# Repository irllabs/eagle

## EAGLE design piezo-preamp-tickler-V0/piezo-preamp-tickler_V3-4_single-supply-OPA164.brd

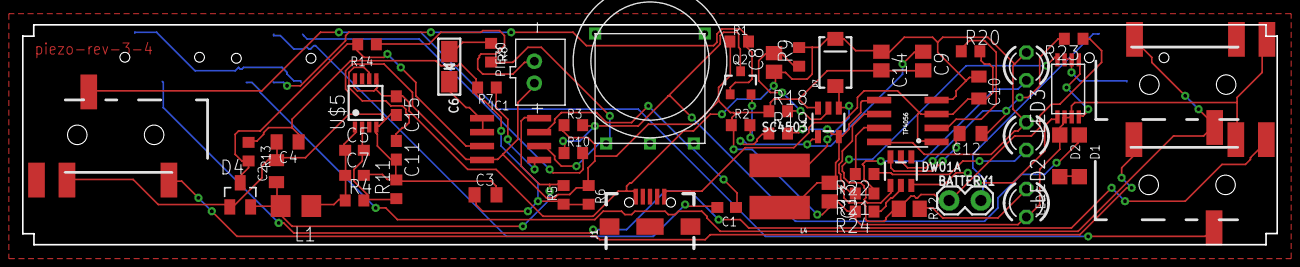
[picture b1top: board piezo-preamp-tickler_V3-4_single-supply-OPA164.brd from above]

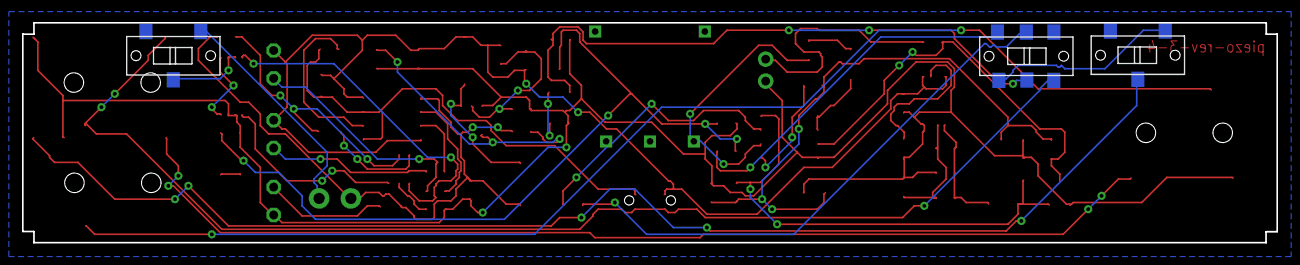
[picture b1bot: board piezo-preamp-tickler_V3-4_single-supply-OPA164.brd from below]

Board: 2 copper layers, 114.3 x 20.0 mm, 62 parts (3 on the bottom side), 44 nets.

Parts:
BATTERY1: 1X02_LOCK
C1, C7, C15: 10uF; C0603
C2, C4, C10, C12: 0.1uF; C0805K
C3: 10uF; C0805K
C5, C11: 10nF; C0603
C6: 100uF; EIA3216-18/A-R
C8: 2.2pf; C0805
C9: 56nf; C0805
C13: 10uF; C0805
C14: 68uF; C0805
D1, D2: SOD123
D4: BAT54S; SOT23
D7: 10BQ015; SMA-DIODE
DW01A: DW01A; SOT23-6
F8205A: F8205A
IC1: OPA1642; SO08
J1: USB-B-MICRO-SMD_RED_PASTE
L1: 100uH; L3225P
L4: 2.7uH; CR54
LED1, LED2, LED3: LED3MM
PIEZO: JST-PH-2-THM
POWER: SPDT; SWITCH_SPDT_CL-SB-12B
Q2: MMBFJ201; SOT23-3
R1: 2.2K; R0603
R2: 1.2K; R0603
R3, R9: 1M; R0603
R4: 91.2k; R0603
R5, R6, R14: 100K; R0603
R7, R8: 220; R0603
R10: 1K; R0603
R11, R18: 100k; R0603
R12: 390; R0805
R13: 10M; R0603
R19: 15k; R0603
R20: 1.2k; R0603
R21, R22: 1k; R0603
R23: nfo; R0603
R24: 100; R0603
SC4503: VREG12_SOT23-5; SOT23-5
SW2-SPST: INPUT-select; SWITCH_SPDT_CL-SB-12B
TO-HEADSET: AUDIO-JACK3LGPADS; AUDIO-JACK-TRRS-SMD
TO-PHONE, TO-PHONE1: AUDIO-JACK3LGPADS; AUDIO-JACK-TRRS-SMD
TP4056: TP4056-CHIP; SO08
U$2: SWITCH_DPDT; SWITCH_DPDT_CL-SB-22B
U$4: POT-THUMB-14MM_ALPHA-RV100F-30-4K1B-B10K-B301
U$5: TPS7A49; MSOP-8

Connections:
+12V: C5.1, C7.1, L1.1, R4.1, U$5.1
GND: C2.2, C3.2, C4.2, C7.2, C9.2, C11.2, C13.2, C14.2, C15.2, D2.C, D4.1, F8205A.P$6, F8205A.P$7, IC1.4, LED1.K, PIEZO.1, R1.1, R2.1, R3.1, R6.1, R11.2, R18.1, R24.2, SC4503.3, TO-HEADSET.RING2, TO-PHONE.RING2, TO-PHONE1.EARTH, U$5.4
unnamed: D1.A, D2.A
unnamed: PIEZO.2, R14.1
unnamed: Q2.2, R2.2
unnamed: IC1.5, R7.1
unnamed: C1.1, IC1.7, U$4.P$3
unnamed: IC1.6, R8.2, U$4.P$1
unnamed: D4.3, IC1.3, R13.2, R14.2
unnamed: D1.C, Q2.3, R3.2, R10.1
unnamed: R10.2, U$2.4
unnamed: TO-PHONE1.RING1, TO-PHONE1.TIP, U$2.3
unnamed: TO-HEADSET.TIP, TO-PHONE.TIP
unnamed: C6.-, R8.1
unnamed: TO-HEADSET.RING1, TO-PHONE.RING1
unnamed: C1.2, U$2.5
unnamed: SW2-SPST.P$2, TO-PHONE.EARTH
unnamed: LED1.A, R12.1
unnamed: SW2-SPST.P$1, U$2.1
unnamed: F8205A.P$2, F8205A.P$3, POWER.P$2
unnamed: BATTERY1.2, POWER.P$1
unnamed: C3.1, C4.1, R5.1, R6.2, R7.2, R13.1
unnamed: C6.+, IC1.1, IC1.2
unnamed: C2.1, D4.2, IC1.8, L1.2, R5.2
unnamed: C5.2, R4.2, R11.1, U$5.2
unnamed: C11.1, U$5.6
unnamed: C9.1, R19.1, SC4503.4
unnamed: C8.2, R9.1, R18.2, SC4503.2
unnamed: D7.A, L4.P$2, SC4503.1
unnamed: C10.2, J1.GND, R20.2, TP4056.1, TP4056.3
unnamed: DW01A.1, F8205A.P$4
unnamed: R20.1, TP4056.2
unnamed: DW01A.3, F8205A.P$5
unnamed: R22.2, TP4056.7
unnamed: R21.2, TP4056.6
unnamed: LED3.K, R21.1
unnamed: LED2.K, R22.1
unnamed: C12.1, DW01A.5, R23.2
unnamed: C12.2, DW01A.6
unnamed: DW01A.2, R24.1
unnamed: F8205A.P$1, F8205A.P$8
SELECT: Q2.1, R1.2, U$2.2
V+: C8.1, C10.1, C14.1, C15.1, D7.C, J1.VBUS, LED2.A, LED3.A, R9.2, TP4056.4, TP4056.8, U$5.5, U$5.8
VBAT: BATTERY1.1, C13.1, L4.P$1, R12.2, R19.2, R23.1, SC4503.5, TP4056.5

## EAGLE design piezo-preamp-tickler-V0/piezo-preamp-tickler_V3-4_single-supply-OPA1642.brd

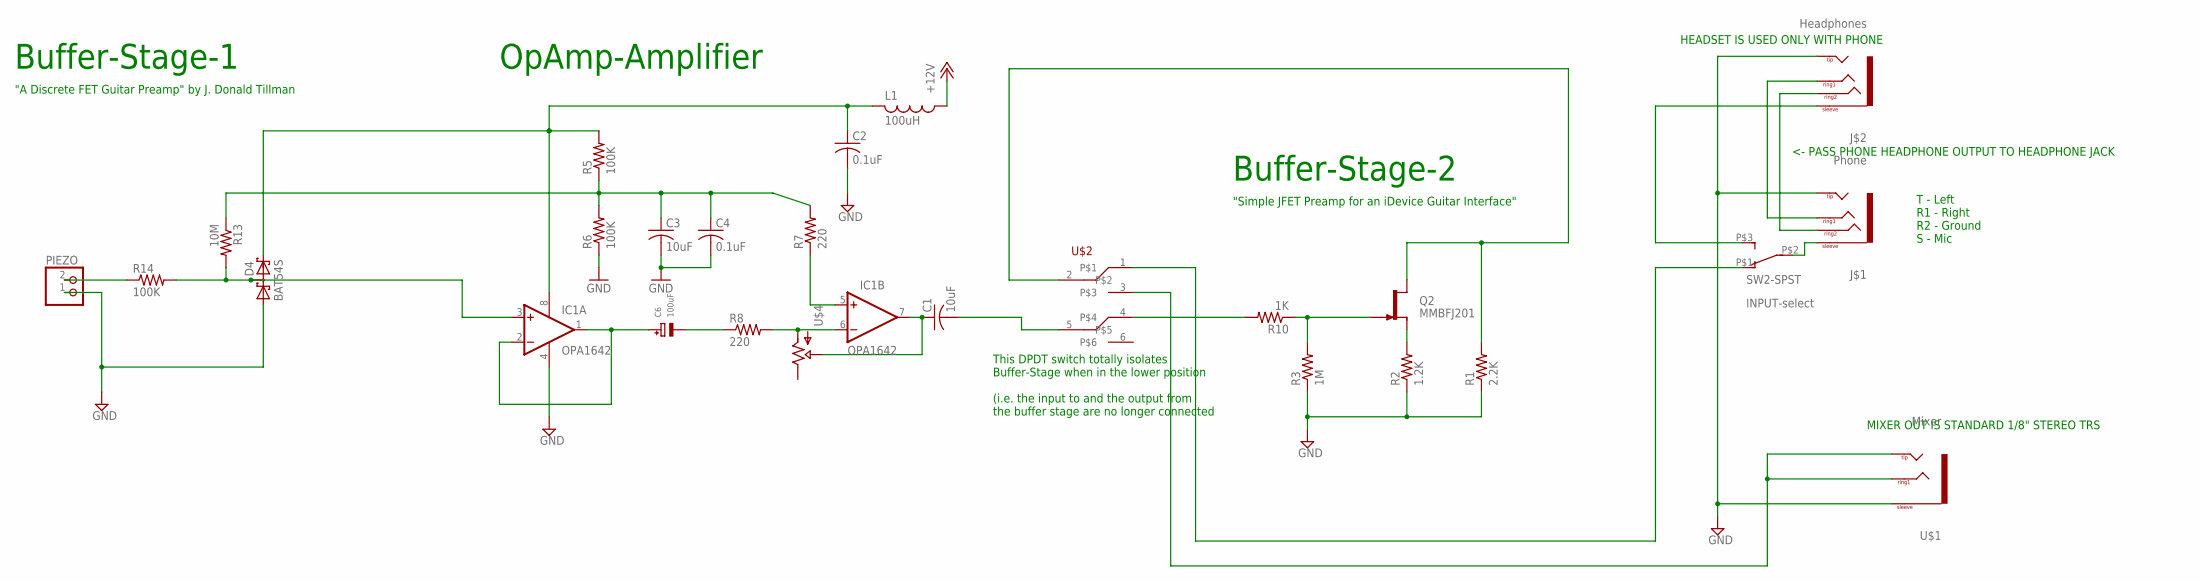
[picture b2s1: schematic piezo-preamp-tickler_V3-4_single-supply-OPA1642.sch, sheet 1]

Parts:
C1: 10uF; C0805
C2, C4: 0.1uF; C0805K
C3: 10uF; C0805K
C6: 100uF; EIA3216-18/A-R
D4: BAT54S; SOT23
IC1: OPA1642; SO08
J$1: Phone; TRRS_SJ-43514-SMT-TR
J$2: Headphones; TRRS_SJ-43514-SMT-TR
L1: 100uH; L3225P
PIEZO: JST_2PIN-THM; JST-PH-2-THM
Q2: MMBFJ201; SOT23-3
R1: 2.2K; R0603
R2: 1.2K; R0603
R3: 1M; R0603
R5, R6, R14: 100K; R0603
R7, R8: 220; R0603
R10: 1K; R0603
R13: 10M; R0603
SW2-SPST: INPUT-select; SWITCH_SPDT_CL-SB-12B
U$1: Mixer; TRS_SJ-3524-SMT
U$2: SWITCH_DPDT; SWITCH_DPDT_CL-SB-22B
U$4: POTPOT-THUMB-ALPHA; POT-THUMB-14MM_ALPHA-RV100F-30-4K1B-B10K-B301

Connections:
+12V: L1.1; also elsewhere on the board
GND: C2.2, C3.2, C4.2, D4.1 (A1), IC1.4 (V-), J$1.TIP, J$2.TIP, PIEZO.1 (2), R1.1, R2.1, R3.1, R6.1, U$1.1 (SLEEVE); also elsewhere on the board
unnamed: PIEZO.2 (1), R14.1
unnamed: Q2.2 (S), R2.2
unnamed: IC1.5 (+IN), R7.1
unnamed: C1.1, IC1.7 (OUT), U$4.P$3 (WIPER)
unnamed: IC1.6 (-IN), R8.2, U$4.P$1 (IN)
unnamed: D4.3 (C1A2), IC1.3 (+IN), R13.2, R14.2
unnamed: Q2.3 (G), R3.2, R10.1
unnamed: R10.2, U$2.4
unnamed: U$1.2 (TIP), U$1.3 (RING1), U$1.4 (TIP), U$2.3
unnamed: J$1.RING1, J$2.RING1
unnamed: C6.-, R8.1
unnamed: J$1.RING2, J$2.RING2
unnamed: C1.2, U$2.5
unnamed: J$1.EARTH (SLEEVE), SW2-SPST.P$2 (2)
unnamed: SW2-SPST.P$1 (1), U$2.1
unnamed: C3.1, C4.1, R5.1, R6.2, R7.2, R13.1
unnamed: C6.+, IC1.1 (OUT), IC1.2 (-IN)
unnamed: C2.1, D4.2 (C2), IC1.8 (V+), L1.2, R5.2
SELECT: Q2.1 (D), R1.2, U$2.2

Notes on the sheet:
Buffer-Stage-1
OpAmp-Amplifier
Buffer-Stage-2
"A Discrete FET Guitar Preamp" by J. Donald Tillman
"Simple JFET Preamp for an iDevice Guitar Interface"
T - Left R1 - Right R2 - Ground S - Mic
HEADSET IS USED ONLY WITH PHONE
MIXER OUT IS STANDARD 1/8" STEREO TRS
<- PASS PHONE HEADPHONE OUTPUT TO HEADPHONE JACK
This DPDT switch totally isolates Buffer-Stage when in the lower position (i.e. the input to and the output from the buffer stage are no longer connected

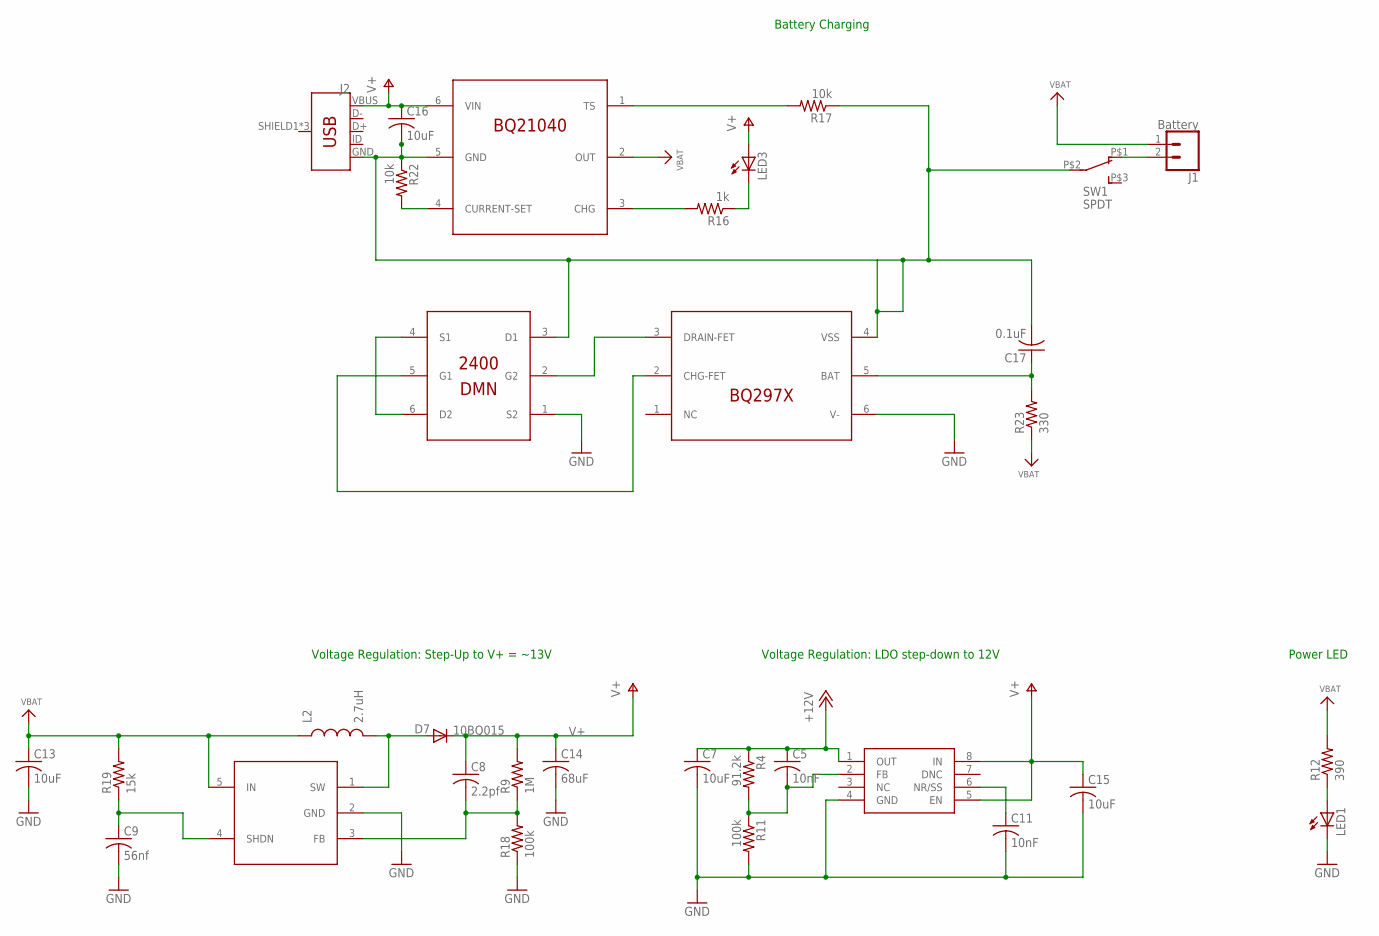
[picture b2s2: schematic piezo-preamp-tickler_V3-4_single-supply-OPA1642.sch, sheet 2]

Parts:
C5, C11: 10nF; C0603
C7, C13, C15: 10uF; C0603
C8: 2.2pf; C0603
C9: 56nf; C0603
C14: 68uF; C0603
C16: 10uF; C0805K
C17: 0.1uF; C0805K
D7: 10BQ015; SMA-DIODE
IC2: TPS7A49; MSOP-8
IC3: DMN2400; SOT-563
IC4: BQ297X; WSON-6
J1: Battery; 1X02_LOCK
J2: USB_MICRO-BREDUCED_PASTE; USB-B-MICRO-SMD_RED_PASTE
L2: 2.7uH; CR54
LED1, LED3: LED3MM
Q1: BQ21040; SOT23-6
Q3: SC4503; SOT23-5
R4: 91.2k; R0603
R9: 1M; R0603
R11, R18: 100k; R0603
R12: 390; R0805
R16: 1k; R0805
R17, R22: 10k; R0805
R19: 15k; R0603
R23: 330; R0805
SW1: SPDT; SWITCH_SPDT_CL-SB-12B

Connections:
+12V: C5.1, C7.1, IC2.1 (OUT), R4.1; also elsewhere on the board
GND: C7.2, C9.2, C11.2, C13.2, C14.2, C15.2, IC2.4 (GND), IC3.1 (S2), IC4.6 (V-), LED1.K (C), Q3.2 (GND), R11.2, R18.1; also elsewhere on the board
GND2: C16.2, C17.2, IC3.3 (D1), IC4.4 (VSS), J2.GND, Q1.5 (GND), R17.1, R22.1, SW1.P$2 (2)
unnamed: LED1.A, R12.1
unnamed: J1.2, SW1.P$1 (1)
unnamed: LED3.K (C), R16.1
unnamed: C5.2, IC2.2 (FB), R4.2, R11.1
unnamed: Q1.3 (CHG), R16.2
unnamed: C11.1, IC2.6 (NR/SS)
unnamed: C9.1, Q3.4 (SHDN), R19.1
unnamed: C8.2, Q3.3 (FB), R9.1, R18.2
unnamed: Q1.1 (TS), R17.2
unnamed: D7.A, L2.P$2 (2), Q3.1 (SW)
unnamed: Q1.4 (CURRENT-SET), R22.2
unnamed: C17.1, IC4.5 (BAT), R23.2
unnamed: IC3.4 (S1), IC3.6 (D2)
unnamed: IC3.5 (G1), IC4.2 (CHG-FET)
unnamed: IC3.2 (G2), IC4.3 (DRAIN-FET)
V+: C8.1, C14.1, C15.1, C16.1, D7.C, IC2.5 (EN), IC2.8 (IN), J2.VBUS, LED3.A, Q1.6 (VIN), R9.2
VBAT: C13.1, J1.1, L2.P$1 (1), Q1.2 (OUT), Q3.5 (IN), R12.2, R19.2, R23.1

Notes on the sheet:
Voltage Regulation: Step-Up to V+ = ~13V
Power LED
Voltage Regulation: LDO step-down to 12V
Battery Charging

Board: 2 copper layers, 58 parts (6 on the bottom side), 39 nets, no tracks yet.

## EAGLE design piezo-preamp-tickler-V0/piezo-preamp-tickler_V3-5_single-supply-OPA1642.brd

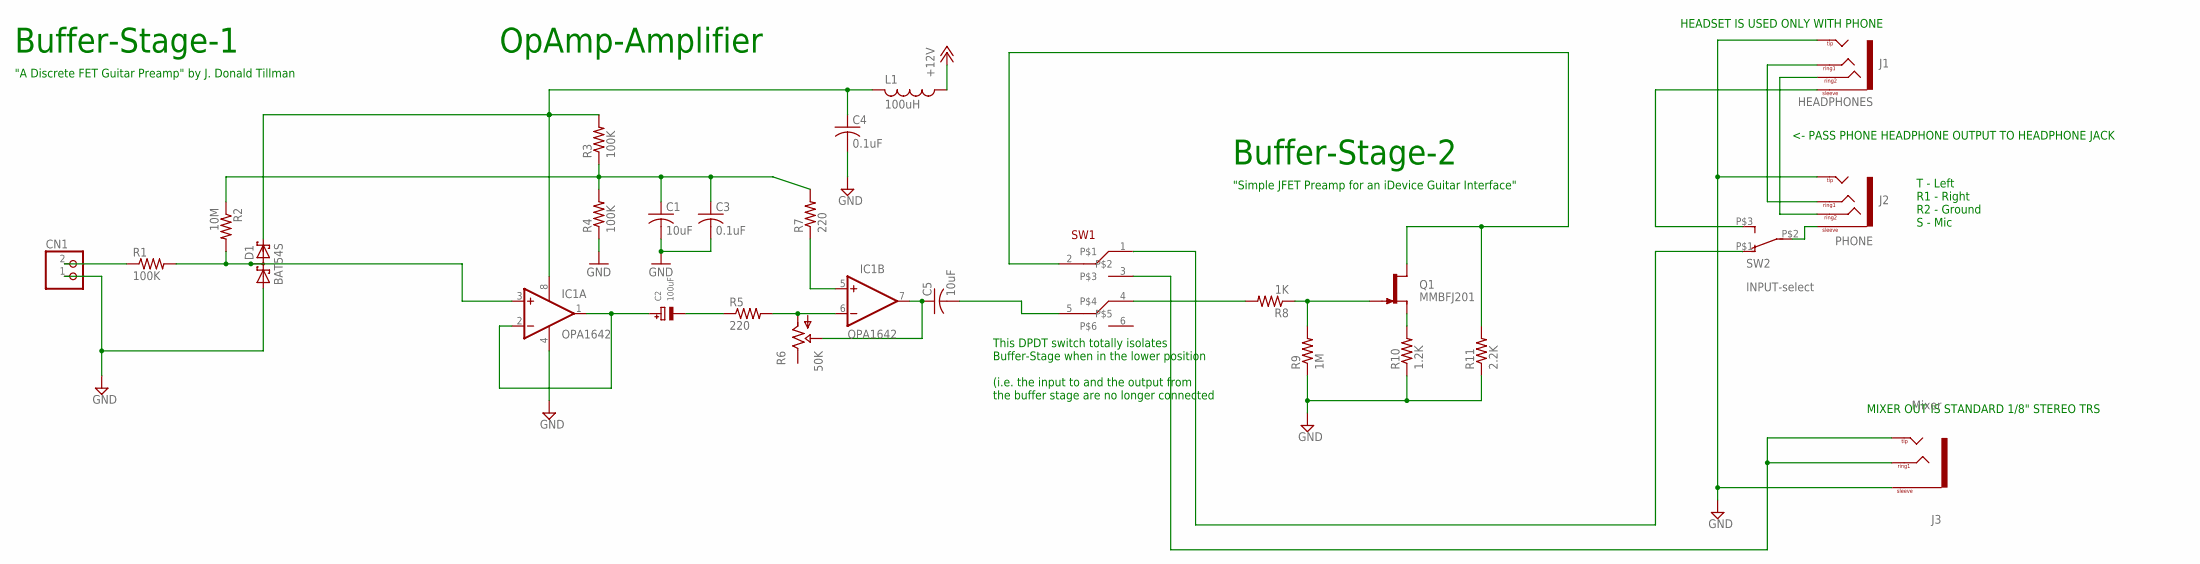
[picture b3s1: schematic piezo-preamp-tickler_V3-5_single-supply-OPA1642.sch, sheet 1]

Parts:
C1: 10uF; C0805K
C2: 100uF; EIA3216-18/A-R
C3, C4: 0.1uF; C0805K
C5: 10uF; C0805
CN1: JST_2PIN-THM; JST-PH-2-THM
D1: BAT54S; SOT23
IC1: OPA1642; SO08
J1: HEADPHONES; TRRS_SJ-43514-SMT-TR
J2: PHONE; TRRS_SJ-43514-SMT-TR
J3: Mixer; TRS_SJ-3524-SMT
L1: 100uH; L3225P
Q1: MMBFJ201; SOT23-3
R1, R3, R4: 100K; R0603
R2: 10M; R0603
R5, R7: 220; R0603
R6: 50K; POT-THUMB-14MM_ALPHA-RV100F-30-4K1B-B10K-B301
R8: 1K; R0603
R9: 1M; R0603
R10: 1.2K; R0603
R11: 2.2K; R0603
SW1: SWITCH_DPDT; SWITCH_DPDT_CL-SB-22B
SW2: INPUT-select; SWITCH_SPDT_CL-SB-12B

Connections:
+12V: L1.1; also elsewhere on the board
GND: C1.2, C3.2, C4.2, CN1.1 (2), D1.1 (A1), IC1.4 (V-), J1.TIP, J2.TIP, J3.1 (SLEEVE), R4.1, R9.1, R10.1, R11.1; also elsewhere on the board
unnamed: CN1.2 (1), R1.1
unnamed: Q1.2 (S), R10.2
unnamed: IC1.5 (+IN), R7.1
unnamed: C5.1, IC1.7 (OUT), R6.P$2 (WIPER)
unnamed: IC1.6 (-IN), R5.2, R6.P$1 (IN)
unnamed: D1.3 (C1A2), IC1.3 (+IN), R1.2, R2.2
unnamed: Q1.3 (G), R8.1, R9.2
unnamed: R8.2, SW1.4
unnamed: J3.2 (TIP), J3.3 (RING1), J3.4 (TIP), SW1.3
unnamed: J1.RING1, J2.RING1
unnamed: C2.-, R5.1
unnamed: J1.RING2, J2.RING2
unnamed: C5.2, SW1.5
unnamed: J2.EARTH (SLEEVE), SW2.P$2 (2)
unnamed: SW1.1, SW2.P$1 (1)
unnamed: C1.1, C3.1, R2.1, R3.1, R4.2, R7.2
unnamed: C2.+, IC1.1 (OUT), IC1.2 (-IN)
unnamed: C4.1, D1.2 (C2), IC1.8 (V+), L1.2, R3.2
SELECT: Q1.1 (D), R11.2, SW1.2

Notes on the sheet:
Buffer-Stage-1
OpAmp-Amplifier
Buffer-Stage-2
"A Discrete FET Guitar Preamp" by J. Donald Tillman
"Simple JFET Preamp for an iDevice Guitar Interface"
T - Left R1 - Right R2 - Ground S - Mic
HEADSET IS USED ONLY WITH PHONE
MIXER OUT IS STANDARD 1/8" STEREO TRS
<- PASS PHONE HEADPHONE OUTPUT TO HEADPHONE JACK
This DPDT switch totally isolates Buffer-Stage when in the lower position (i.e. the input to and the output from the buffer stage are no longer connected

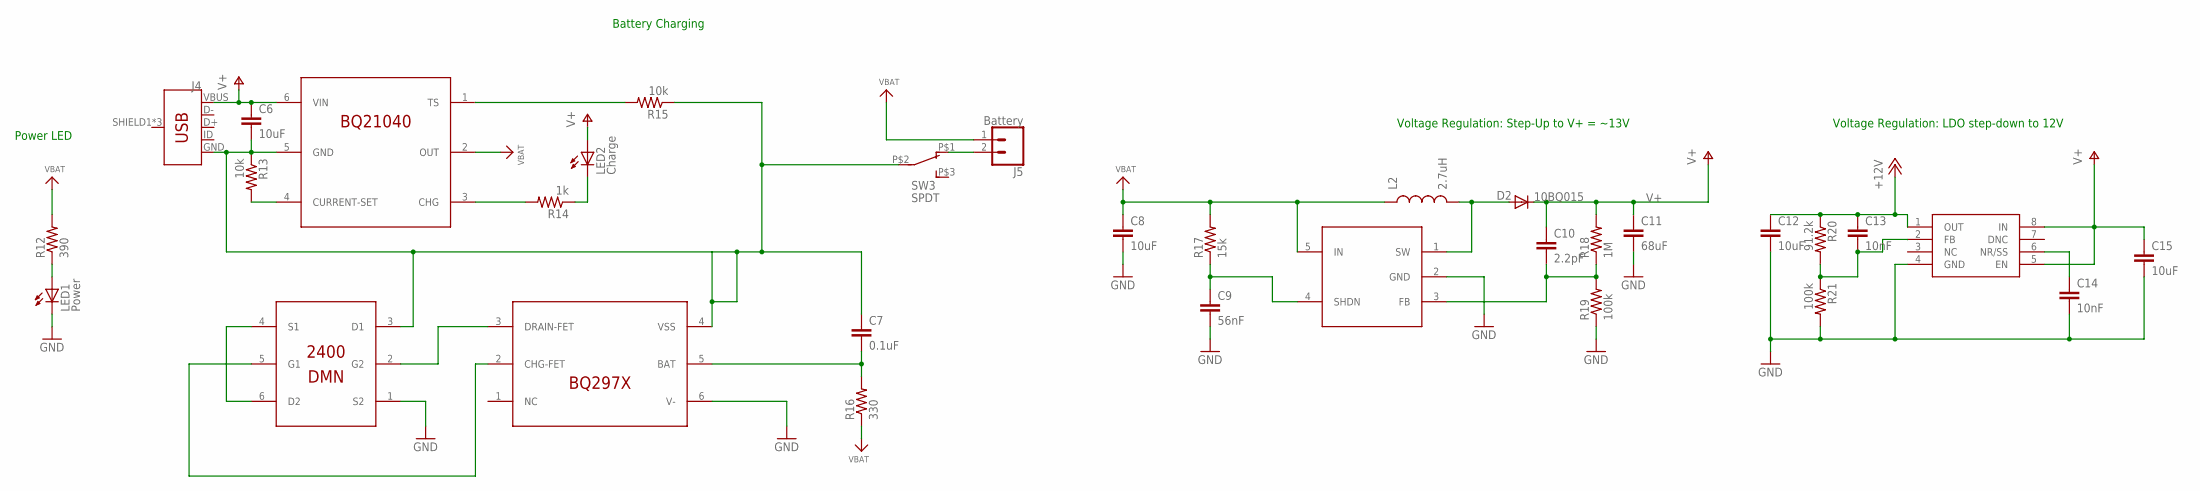
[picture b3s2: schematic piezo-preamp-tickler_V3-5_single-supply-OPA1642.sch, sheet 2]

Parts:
C6, C8, C12, C15: 10uF; C0603
C7: 0.1uF; C0603
C9: 56nF; C0603
C10: 2.2pF; C0603
C11: 68uF; C1206
C13, C14: 10nF; C0603
D2: 10BQ015; SMA-DIODE
IC2: DMN2400; SOT-563
IC3: BQ21040; SOT23-6
IC4: BQ297X; WSON-6
IC5: SC4503; SOT23-5
IC6: TPS7A49; MSOP-8
J4: USB_MICRO-BREDUCED_PASTE; USB-B-MICRO-SMD_RED_PASTE
J5: Battery; 1X02_LOCK
L2: 2.7uH; CR54
LED1: Power; LED3MM
LED2: Charge; LED3MM
R12: 390; R0603
R13, R15: 10k; R0603
R14: 1k; R0603
R16: 330; R0603
R17: 15k; R0603
R18: 1M; R0603
R19, R21: 100k; R0603
R20: 91.2k; R0603
SW3: SPDT; SWITCH_SPDT_CL-SB-12B

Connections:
+12V: C12.1, C13.1, IC6.1 (OUT), R20.1; also elsewhere on the board
GND: C8.2, C9.2, C11.2, C12.2, C14.2, C15.2, IC2.1 (S2), IC4.6 (V-), IC5.2 (GND), IC6.4 (GND), LED1.K (C), R19.1, R21.2; also elsewhere on the board
GND2: C6.2, C7.1, IC2.3 (D1), IC3.5 (GND), IC4.4 (VSS), J4.GND, R13.1, R15.1, SW3.P$2 (2)
unnamed: LED1.A, R12.1
unnamed: J5.2, SW3.P$1 (1)
unnamed: LED2.K (C), R14.1
unnamed: C13.2, IC6.2 (FB), R20.2, R21.1
unnamed: IC3.3 (CHG), R14.2
unnamed: C14.1, IC6.6 (NR/SS)
unnamed: C9.1, IC5.4 (SHDN), R17.1
unnamed: C10.2, IC5.3 (FB), R18.1, R19.2
unnamed: IC3.1 (TS), R15.2
unnamed: D2.A, IC5.1 (SW), L2.P$2 (2)
unnamed: IC3.4 (CURRENT-SET), R13.2
unnamed: C7.2, IC4.5 (BAT), R16.2
unnamed: IC2.4 (S1), IC2.6 (D2)
unnamed: IC2.5 (G1), IC4.2 (CHG-FET)
unnamed: IC2.2 (G2), IC4.3 (DRAIN-FET)
V+: C6.1, C10.1, C11.1, C15.1, D2.C, IC3.6 (VIN), IC6.5 (EN), IC6.8 (IN), J4.VBUS, LED2.A, R18.2
VBAT: C8.1, IC3.2 (OUT), IC5.5 (IN), J5.1, L2.P$1 (1), R12.2, R16.1, R17.2

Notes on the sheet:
Voltage Regulation: Step-Up to V+ = ~13V
Power LED
Voltage Regulation: LDO step-down to 12V
Battery Charging

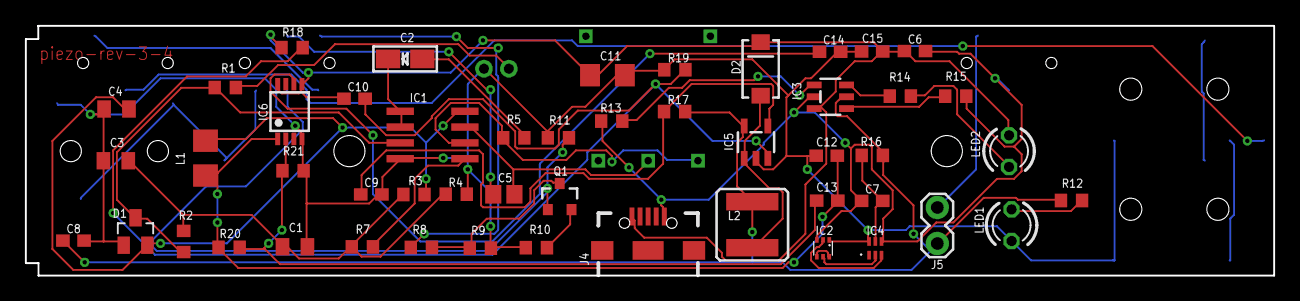
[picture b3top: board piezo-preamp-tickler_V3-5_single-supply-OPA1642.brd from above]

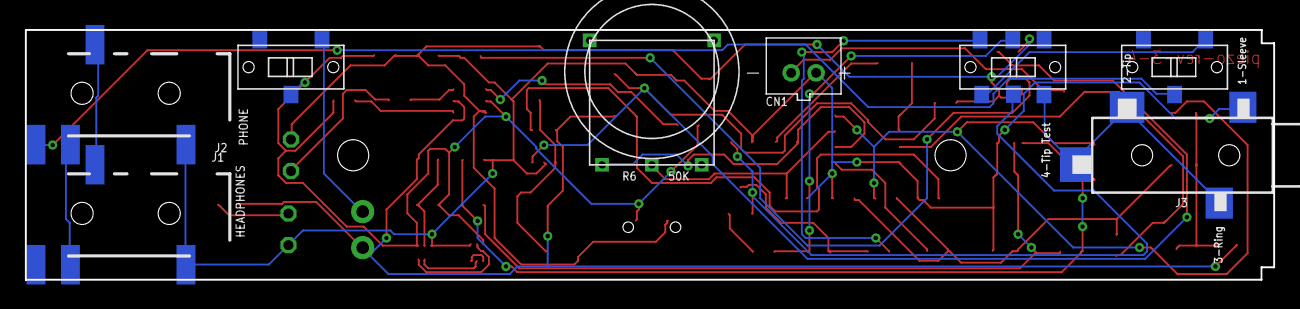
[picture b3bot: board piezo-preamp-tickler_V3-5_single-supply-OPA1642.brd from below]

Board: 2 copper layers, 100.3 x 20.1 mm, 58 parts (8 on the bottom side), 39 nets.

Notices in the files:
parts and their libraries:
SparkFun-Connectors: Licensing: Creative Commons ShareAlike 4.0 International - https://creativecommons.org/licenses/by-sa/4.0
microbuilder: This work is placed in the public domain, and may be freely used for commercial and non-commercial work with the following conditions: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
